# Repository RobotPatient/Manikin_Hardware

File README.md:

# Manikin_Hardware
This repo contains the current hardware for the SensorHubs and mainboard of the manikin (BLS - Basic Life Support)

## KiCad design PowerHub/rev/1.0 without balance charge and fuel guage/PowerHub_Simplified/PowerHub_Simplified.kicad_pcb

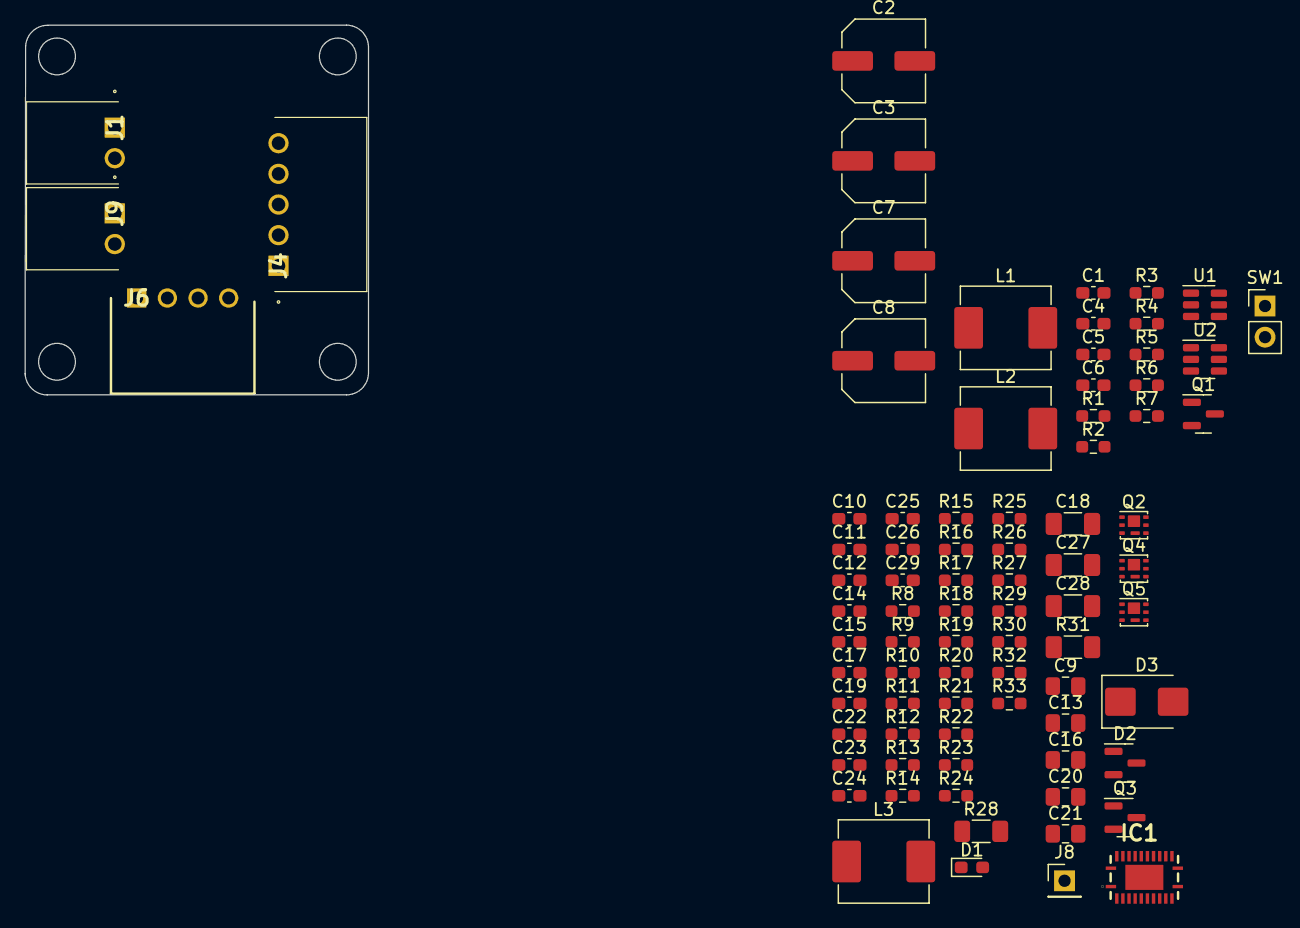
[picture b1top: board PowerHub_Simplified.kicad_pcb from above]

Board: 2 copper layers, 28.0 x 30.2 mm, 82 parts (0 on the bottom side), 44 nets, no tracks yet.

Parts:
C1, C4, C5, C6, C15, C17, C22, C25, C26: 100n; C_0603_1608Metric_Pad1.08x0.95mm_HandSolder
C2, C3, C7, C8: 68uF; C_Elec_6.3x7.7
C9: 2.2uF; C_0805_2012Metric_Pad1.18x1.45mm_HandSolder
C10: 330p; C_0603_1608Metric_Pad1.08x0.95mm_HandSolder
C11: 4700p; C_0603_1608Metric_Pad1.08x0.95mm_HandSolder
C12, C23: 0.047u; C_0603_1608Metric_Pad1.08x0.95mm_HandSolder
C13, C16, C20, C21: 1u; C_0805_2012Metric_Pad1.18x1.45mm_HandSolder
C14: 0.1u; C_0603_1608Metric_Pad1.08x0.95mm_HandSolder
C18, C27, C28: 10u; C_1206_3216Metric_Pad1.33x1.80mm_HandSolder
C19: 22p; C_0603_1608Metric_Pad1.08x0.95mm_HandSolder
C24: 10u; C_0603_1608Metric_Pad1.08x0.95mm_HandSolder
C29: 1u; C_0603_1608Metric_Pad1.08x0.95mm_HandSolder
D1: CHARGING_LED; LED_0603_1608Metric_Pad1.05x0.95mm_HandSolder
D2: BAT54C; SOT-23
D3: B220; D_SMB
IC1: BQ24171RGYR; RGY_R-PVQFN-N24_
J1: Charger; 1814773
J4: HUB_CONN_1_W_VBUS; 1814809
J6: HUB_CONN_2; SHDRRA4W60P0X250_1X4_1170X750X510P
J8: charger_temp_probe; PinHeader_1x01_P2.54mm_Vertical
J9: Battery; 1814773
L1: 3.3uH; L_Abracon_ASPI-0630LR
L2: 2.2uH; L_Abracon_ASPI-0630LR
L3: 3.3u; L_Abracon_ASPI-0630LR
Q1: BC817; SOT-23
Q2, Q4: CSD17313Q2; Texas_DQK
Q3: BSS138; SOT-23
Q5: CSD25302Q2; Texas_DQK
R1: 56k; R_0603_1608Metric_Pad0.98x0.95mm_HandSolder
R2, R4, R7: 10k; R_0603_1608Metric_Pad0.98x0.95mm_HandSolder
R3, R9: 33k; R_0603_1608Metric_Pad0.98x0.95mm_HandSolder
R5, R33: 1k; R_0603_1608Metric_Pad0.98x0.95mm_HandSolder
R6: 18k; R_0603_1608Metric_Pad0.98x0.95mm_HandSolder
R8: 220k; R_0603_1608Metric_Pad0.98x0.95mm_HandSolder
R10, R30: 100k; R_0603_1608Metric_Pad0.98x0.95mm_HandSolder
R11: 30k; R_0603_1608Metric_Pad0.98x0.95mm_HandSolder
R12, R13: 3.9; R_0603_1608Metric_Pad0.98x0.95mm_HandSolder
R14: 6.8k; R_0603_1608Metric_Pad0.98x0.95mm_HandSolder
R15: 390k; R_0603_1608Metric_Pad0.98x0.95mm_HandSolder
R16: 39k; R_0603_1608Metric_Pad0.98x0.95mm_HandSolder
R17: 2.2k; R_0603_1608Metric_Pad0.98x0.95mm_HandSolder
R18, R20, R27: 3.9k; R_0603_1608Metric_Pad0.98x0.95mm_HandSolder
R19: 10; R_0603_1608Metric_Pad0.98x0.95mm_HandSolder
R21, R32: 1M; R_0603_1608Metric_Pad0.98x0.95mm_HandSolder
R22: 3M; R_0603_1608Metric_Pad0.98x0.95mm_HandSolder
R23, R29: 500k; R_0603_1608Metric_Pad0.98x0.95mm_HandSolder
R24: 0; R_0603_1608Metric_Pad0.98x0.95mm_HandSolder
R25: 100; R_0603_1608Metric_Pad0.98x0.95mm_HandSolder
R26: DNP; R_0603_1608Metric_Pad0.98x0.95mm_HandSolder
R28: 0.01; R_1206_3216Metric_Pad1.30x1.75mm_HandSolder
R31: 0.01; C_1206_3216Metric_Pad1.33x1.80mm_HandSolder
SW1: SW_SPST; PinHeader_1x02_P2.54mm_Vertical
U1, U2: TPS565208; SOT-23-6

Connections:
!BATTDRV: IC1.19 (~BATDRV), R33.2
+3.3V: C8.1, J4.3, J6.3, L2.2, R3.1
+5V: C7.1, J4.1, L1.2, R1.1
/Battery_charger/BATTERY+: C19.1, C22.1, C26.2, C27.1, C28.1, C29.1, D2.2, IC1.15 (SRN), J9.2, Q5.4 (D), Q5.7 (D), R29.1, R31.2
/Battery_charger/CHARGER_PWR_IN+: C11.1, D2.1, J1.2, Q2.1 (D), Q2.2 (D), Q2.5 (D), Q2.6 (D), Q2.8 (D), R12.1, R13.1, R14.2, R15.1
ACDRV: IC1.8 (ACDRV), R20.2
ACP: C15.1, C17.1, IC1.6 (ACP), Q4.4 (S), Q4.7 (S), R28.1
ACSET: IC1.17 (ACSET), R10.2, R11.1
CMSRC: IC1.7 (CMSRC), R27.2
EN: Q1.2 (E), R7.1, U1.5 (EN), U2.5 (EN)
GND: C1.1, C2.2, C3.2, C4.1, C7.2, C8.2, C9.2, C10.2, C13.2, C14.2, C15.2, C16.2, C18.2, C20.2, C21.2, C22.2, C24.2, C25.2, C27.2, C28.2, C29.2, D3.2 (A), IC1.22 (PGND_1), IC1.23 (PGND_2), IC1.25 (AGND), J1.1, J4.2, J6.4, J9.1, R2.2, R4.2, R7.2, R9.2, R11.2, R16.2, R18.2, R21.1, R26.2, R30.2, R32.2, U1.1 (GND), U2.1 (GND)
ISET: IC1.13 (ISET), R8.2, R9.1
unnamed: C9.1, R12.2, R13.2
unnamed: C14.1, R24.2
unnamed: D1.2 (A), R14.1
unnamed: D2.3, R19.1
unnamed: C23.1, D3.1 (K), IC1.1 (SW_1), IC1.24 (SW_2), L3.1
unnamed: C13.1, IC1.4 (AVCC), R19.2
unnamed: C23.2, IC1.21 (BTST)
unnamed: C19.2, IC1.14 (FB), R29.2, R30.1
unnamed: C20.1, IC1.20 (REGN)
unnamed: C25.1, C26.1, IC1.16 (SRP), L3.2, R31.1
unnamed: IC1.10 (TS), R25.2
unnamed: J8.1, R17.2, R18.1, R25.1
unnamed: Q1.1 (B), SW1.2 (B)
unnamed: Q1.3 (C), R6.2
unnamed: C11.2, C12.2, Q2.3 (G), Q3.3 (D), Q4.3 (G), R20.1, R23.2
unnamed: Q3.1 (G), R21.2, R22.1
unnamed: C12.1, Q2.4 (S), Q2.7 (S), Q3.2 (S), Q4.1 (D), Q4.2 (D), Q4.5 (D), Q4.6 (D), Q4.8 (D), R22.2, R23.1, R27.1
unnamed: Q5.3 (G), R32.1, R33.1
unnamed: R5.1, SW1.1 (A)
unnamed: C5.2, L1.1, U1.2 (SW)
unnamed: C5.1, U1.6 (VBST)
unnamed: C6.2, L2.1, U2.2 (SW)
unnamed: C6.1, U2.6 (VBST)
OVPSET: C10.1, IC1.18 (OVPSET), R15.2, R16.1
SCL: J4.4, J6.2
SDA: J4.5, J6.1
STAT: D1.1 (K), IC1.9 (STAT)
TTC: IC1.11 (TTC), R24.1, R26.1
VCCQ: C1.2, C2.1, C3.1, C4.2, C17.2, C18.1, C21.1, C24.1, IC1.2 (PVCC_1), IC1.3 (PVCC_2), IC1.5 (ACN), Q5.1 (S), Q5.2 (S), Q5.5 (S), Q5.6 (S), Q5.8 (S), R5.2, R6.1, R28.2, U1.3 (VIN), U2.3 (VIN)
VFB_3.3: R3.2, R4.1, U2.4 (VFB)
VFB_5: R1.2, R2.1, U1.4 (VFB)
VREF: C16.1, IC1.12 (VREF), R8.1, R10.1, R17.1

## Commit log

2023-02-05 -add files for Mainbord, SensorHub, ThoraxSensor and Bosch_BMI_BMM
2023-02-13 -add schematics for sensorhub rev 1.1 and rev 1.1.1
2023-02-13 -add schematic for mainbord
2023-02-13 -add schematic for bmi270 sensor
2023-02-13 -enh move mainbord schematic into folder with revision
2023-02-13 -add new design files for lite versions of actuatorhub and sensorhub
2023-02-13 -enh move pdf files to more sensible location
2023-02-13 -add pdf schematic for new sensorhub, actuatorhub and simbox
2023-02-15 -add eagle files for various sensors
2023-02-15 -add eagle files for Communication modules
2023-02-15 -add PDF schematic for sensors and communication modules
2023-02-17 -add ActuatorHub_Lite rev 1.1
2023-03-15 -add Rev 1.1.2 schematic, board and pdf of schematic
2023-05-11 Added Pro version for ActuatorHub with SRAM
2023-05-11 SoundHub Pro SAMD51 v1.0 added
2023-05-11 Added final version with BMM150 fix
2023-05-11 Update .gitignore
    -add .DS_Store files (Mac)
2023-05-11 -rm mac file
2023-05-11 restructured ActuatorHub
2023-05-11 -add PDF schematic for rev 1.0.1
2023-09-22 -add schematic for new powerhub
2023-09-23 -add new version with charger circuit
